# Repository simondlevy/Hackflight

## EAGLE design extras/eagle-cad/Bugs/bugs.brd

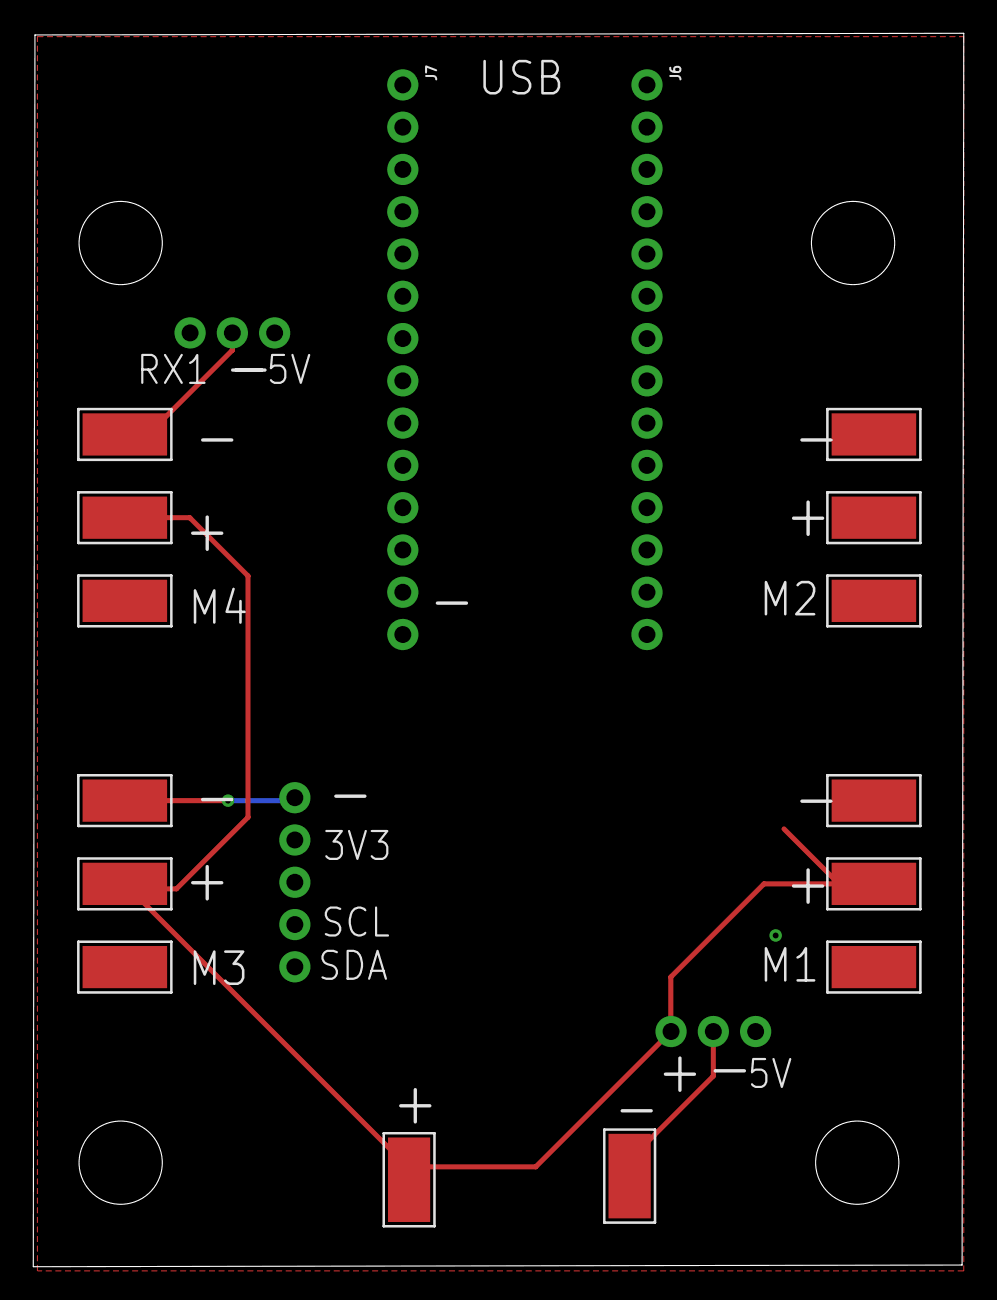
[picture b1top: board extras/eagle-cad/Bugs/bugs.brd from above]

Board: 2 copper layers, 55.9 x 74.1 mm, 19 parts (1 on the bottom side), 10 nets.

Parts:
GND, GND1, GND2, GND3, GND4: WIREPADSMD5-2,5; 5-2,5
J3, J5: 1X03_NO_SILK
J4: 1X05_NO_SILK
J6, J7: 1X14_NO_SILK
M1, M2, M3, M4: WIREPADSMD5-2,5; 5-2,5
VBAT, VBAT1, VBAT2, VBAT3, VBAT4: WIREPADSMD5-2,5; 5-2,5

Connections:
3V3: J4.4, J6.3
5V: J3.1, J5.1, J6.1
GND: GND.1, GND1.1, GND2.1, GND3.1, GND4.1, J3.2, J4.5, J5.2, J6.2, J7.1
M1: J7.5, M1.1
M2: J7.6, M2.1
M3: J7.7, M3.1
M4: J7.10, M4.1
RX1: J5.3, J7.2
SCL: J4.2, J7.8
VBAT: J3.3, VBAT.1, VBAT1.1, VBAT2.1, VBAT3.1, VBAT4.1

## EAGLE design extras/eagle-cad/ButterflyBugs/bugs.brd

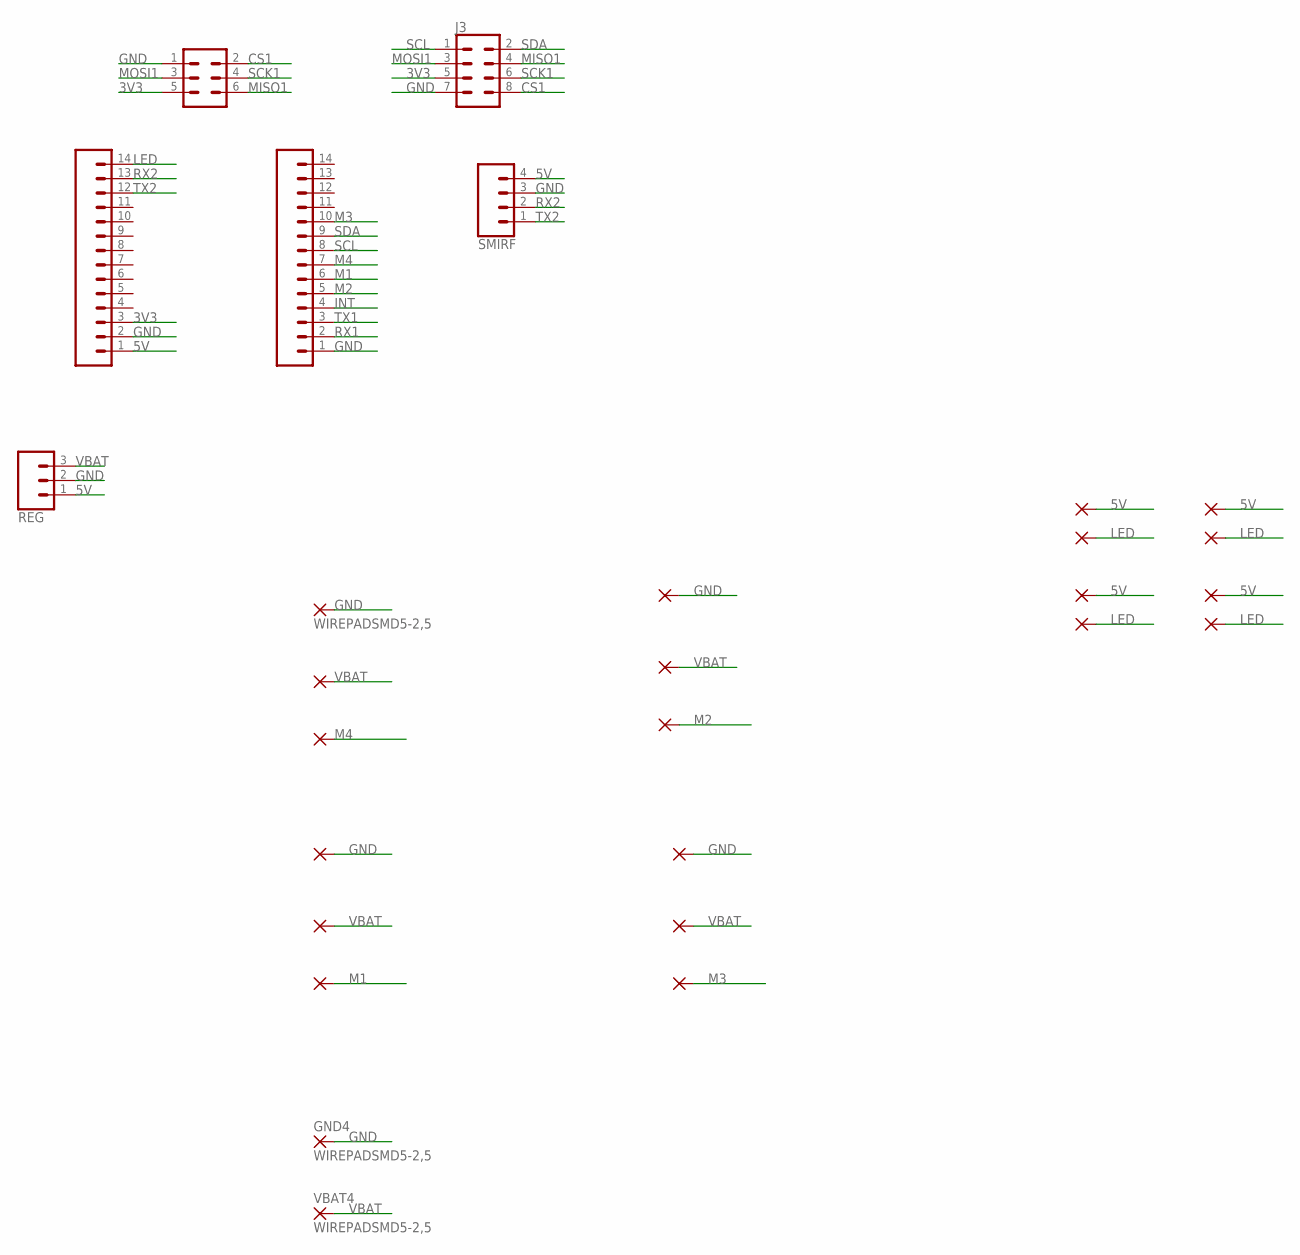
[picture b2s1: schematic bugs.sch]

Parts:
GND, GND1, GND2, GND3, GND4: WIREPADSMD5-2,5; 5-2,5
J1: CONN_03X2NO_SILK; 2X3-NS
J3: CONN_04X2; 2X4
J6, J7: CONN_14NO_SILK; 1X14_NO_SILK
M1, M2, M3, M4: WIREPADSMD5-2,5; 5-2,5
PAD1, PAD2, PAD3, PAD4, PAD5, PAD6, PAD7, PAD8: SMD2; SMD1,27-2,54
REG: REG; 1X03_NO_SILK
SMIRF: SMIRF; 1X04_NO_SILK
VBAT, VBAT1, VBAT2, VBAT3, VBAT4: WIREPADSMD5-2,5; 5-2,5

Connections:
3V3: J1.5, J3.5, J6.3
5V: J6.1, PAD1.1, PAD3.1, PAD5.1, PAD7.1, REG.1, SMIRF.4
CS1: J1.2, J3.8
GND: GND.1, GND1.1, GND2.1, GND3.1, GND4.1, J1.1, J3.7, J6.2, J7.1, REG.2, SMIRF.3
INT: J7.4
LED: J6.14, PAD2.1, PAD4.1, PAD6.1, PAD8.1
M1: J7.6, M1.1
M2: J7.5, M2.1
M3: J7.10, M3.1
M4: J7.7, M4.1
MISO1: J1.6, J3.4
MOSI1: J1.3, J3.3
RX1: J7.2
RX2: J6.13, SMIRF.2
SCK1: J1.4, J3.6
SCL: J3.1, J7.8
SDA: J3.2, J7.9
TX1: J7.3
TX2: J6.12, SMIRF.1
VBAT: REG.3, VBAT.1, VBAT1.1, VBAT2.1, VBAT3.1, VBAT4.1

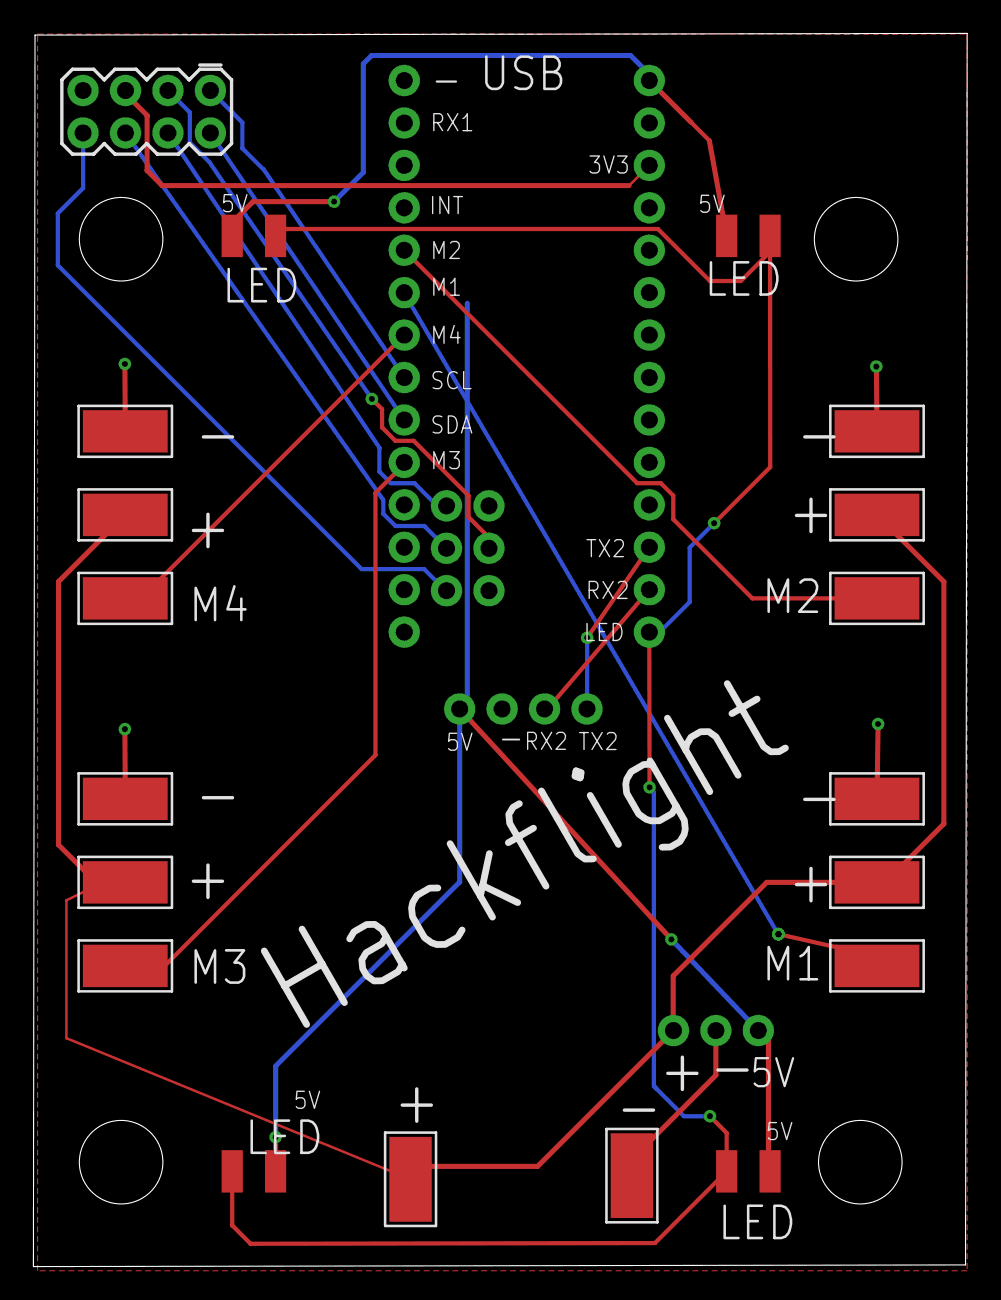
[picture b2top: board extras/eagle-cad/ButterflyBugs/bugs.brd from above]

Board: 2 copper layers, 55.9 x 73.8 mm, 28 parts (0 on the bottom side), 17 nets.

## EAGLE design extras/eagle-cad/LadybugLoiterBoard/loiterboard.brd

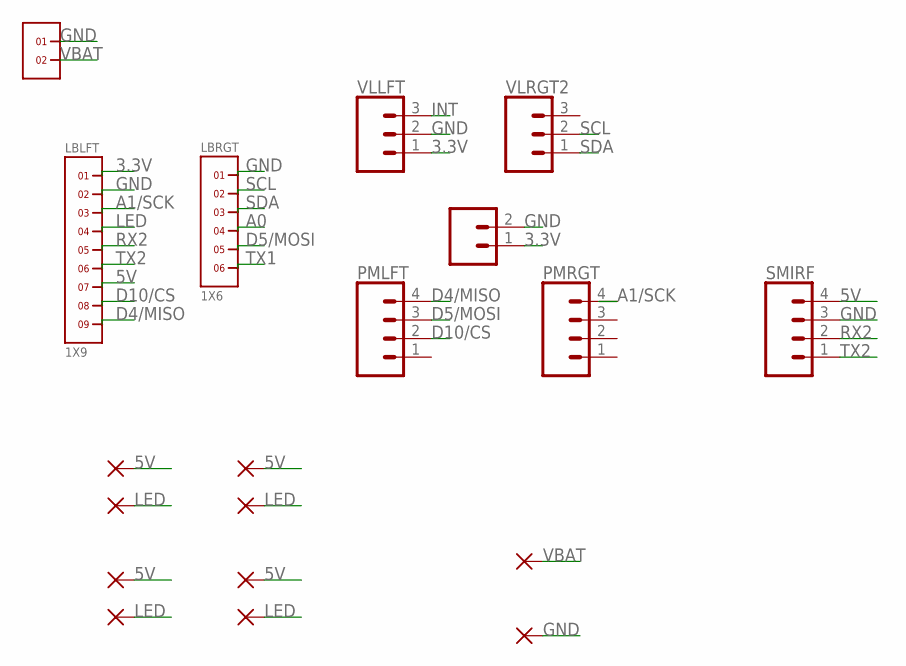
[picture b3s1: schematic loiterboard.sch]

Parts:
LBLFT: 1X9
LBRGT: 1X6
PAD1, PAD2, PAD3, PAD4, PAD5, PAD7, PAD8, PAD9, PAD10: SMD2; SMD1,27-2,54
PAD6: LED; SMD1,27-2,54
PMLFT: CONN_04; 1X04
PMRGT: CONN_04; 1X04
PWPWR: CONN_02; 1X02
SMIRF: CONN_04; 1X04
U$1: 1X2
VLLFT: CONN_03; 1X03
VLRGT2: CONN_03; 1X03

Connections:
3.3V: LBLFT.1, PWPWR.1, VLLFT.1
5V: LBLFT.7, PAD1.1, PAD3.1, PAD5.1, PAD7.1, SMIRF.4
A0: LBRGT.4
A1/SCK: LBLFT.3, PMRGT.4
D4/MISO: LBLFT.9, PMLFT.4
D5/MOSI: LBRGT.5, PMLFT.3
D10/CS: LBLFT.8, PMLFT.2
GND: LBLFT.2, LBRGT.1, PAD10.1, PWPWR.2, SMIRF.3, U$1.1, VLLFT.2
INT: VLLFT.3
LED: LBLFT.4, PAD2.1, PAD4.1, PAD6.1, PAD8.1
RX2: LBLFT.5, SMIRF.2
SCL: LBRGT.2, VLRGT2.2
SDA: LBRGT.3, VLRGT2.1
TX1: LBRGT.6
TX2: LBLFT.6, SMIRF.1
VBAT: PAD9.1, U$1.2

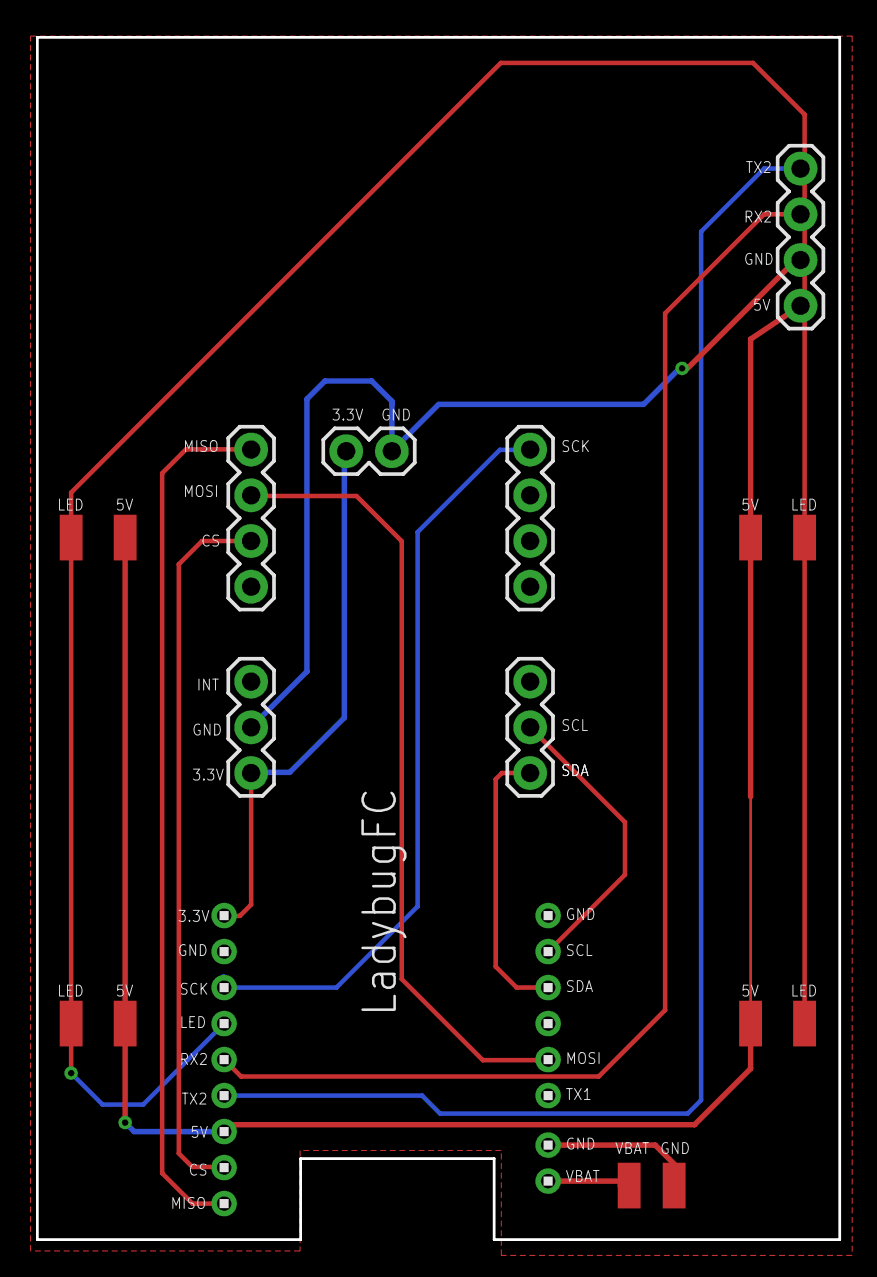
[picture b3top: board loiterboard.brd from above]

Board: 2 copper layers, 44.6 x 66.8 mm, 19 parts (0 on the bottom side), 13 nets.

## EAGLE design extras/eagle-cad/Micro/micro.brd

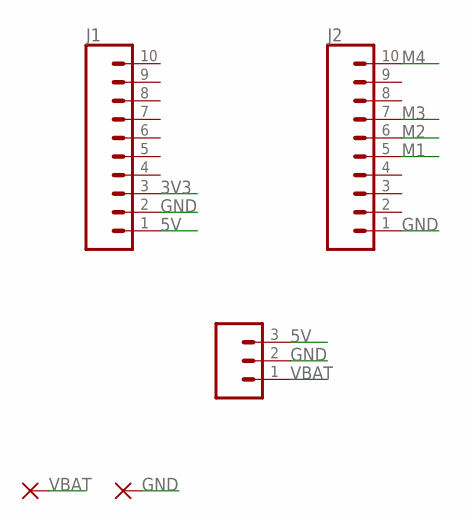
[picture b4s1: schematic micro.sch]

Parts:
J1, J2: CONN_10NO_SILK_PTH_FEMALE; 1X10_NO_SILK
J3: CONN_031X03_NO_SILK; 1X03_NO_SILK
PAD1, PAD2: SMD5; SMD2,54-5,08

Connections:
3V3: J1.3
5V: J1.1, J3.3
GND: J1.2, J2.1, J3.2, PAD2.1
M1: J2.5
M2: J2.6
M3: J2.7
M4: J2.10
VBAT: J3.1, PAD1.1

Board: 2 copper layers, 5 parts (0 on the bottom side), 3 nets, no tracks yet.

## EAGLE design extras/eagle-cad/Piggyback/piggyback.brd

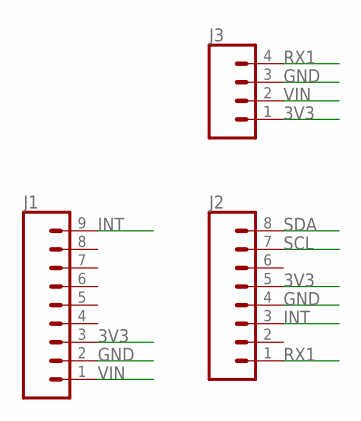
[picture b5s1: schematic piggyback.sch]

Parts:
J1: CONN_09NO_SILK; 1X09_NO_SILK
J2: CONN_08NO_SILK_FEMALE_PTH; 1X08_NO_SILK
J3: CONN_041X04_NO_SILK; 1X04_NO_SILK

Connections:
3V3: J1.3, J2.5, J3.1
GND: J1.2, J2.4, J3.3
INT: J1.9, J2.3
RX1: J2.1, J3.4
SCL: J2.7
SDA: J2.8
VIN: J1.1, J3.2

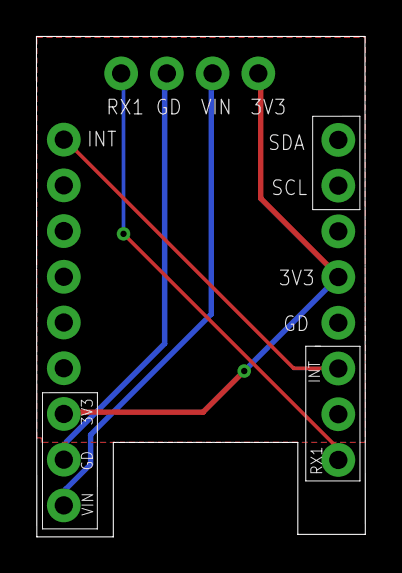
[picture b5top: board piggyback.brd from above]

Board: 2 copper layers, 18.3 x 27.8 mm, 3 parts (0 on the bottom side), 5 nets.

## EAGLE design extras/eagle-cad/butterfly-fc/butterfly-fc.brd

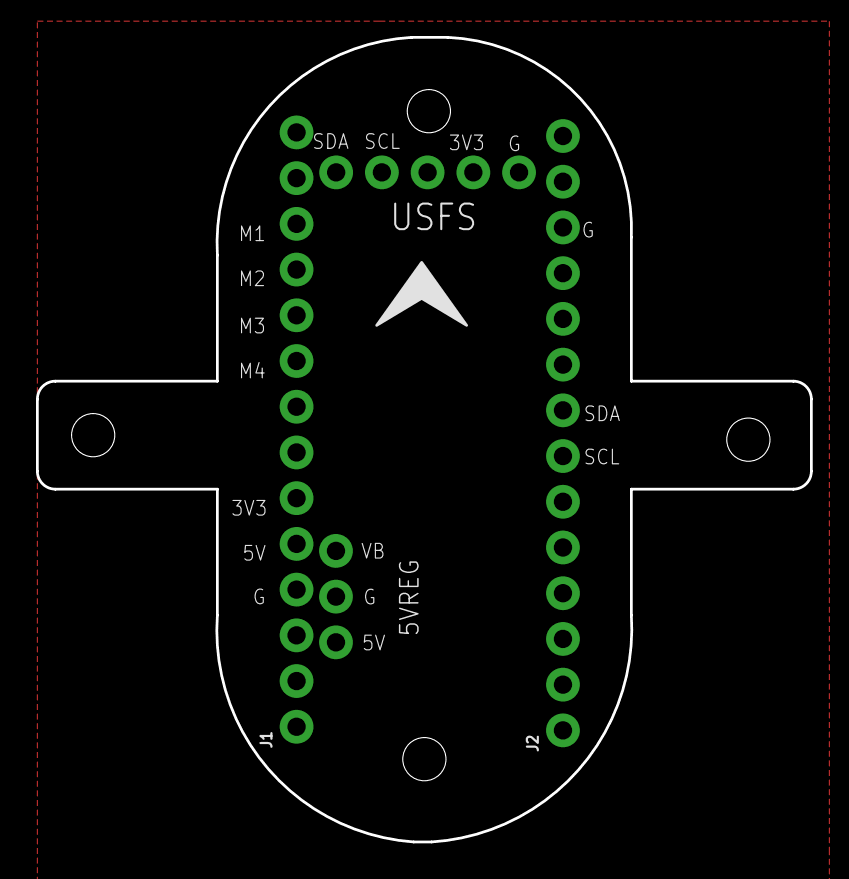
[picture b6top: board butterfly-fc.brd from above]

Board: 2 copper layers, 43.0 x 44.7 mm, 4 parts (0 on the bottom side), 4 nets, no tracks yet.

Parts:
5VREG: 1X03_NO_SILK
J1, J2: 1X14_NO_SILK
USFS: 1X05_NO_SILK

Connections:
3V3: J1.3, USFS.4
GND: 5VREG.2, J1.2, J2.1, USFS.5
SCL: J2.8, USFS.2
SDA: J2.9, USFS.1

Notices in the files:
parts and their libraries:
SparkFun-Connectors: Licensing: Creative Commons ShareAlike 4.0 International - https://creativecommons.org/licenses/by-sa/4.0
